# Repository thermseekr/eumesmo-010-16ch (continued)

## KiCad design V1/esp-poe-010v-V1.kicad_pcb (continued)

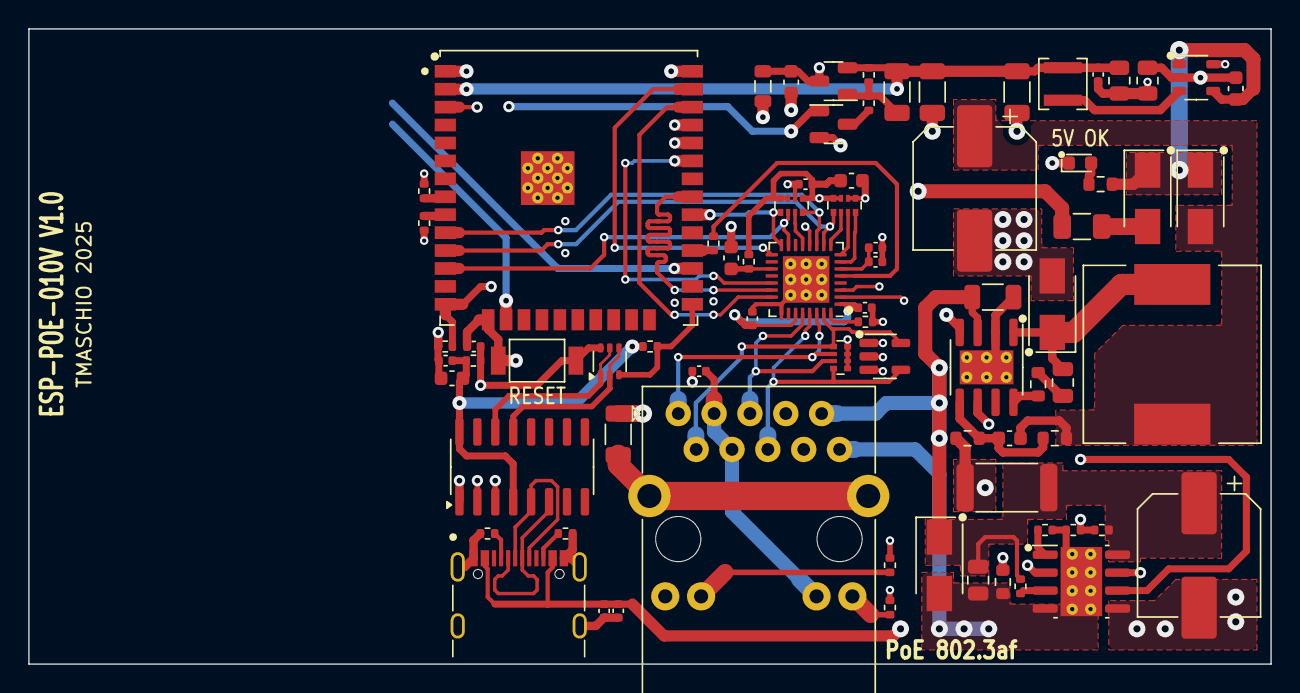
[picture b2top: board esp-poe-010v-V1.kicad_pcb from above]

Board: 4 copper layers, 88.0 x 45.0 mm, 77 parts (0 on the bottom side), 64 nets.

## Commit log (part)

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2025-12-13 Deleted unused files
2025-12-19 dev time
2026-06-18 Starting for an existing project.
2026-06-18 Development.
2026-06-18 Renamed all files to reflect the eumesmo branding.
2026-06-18 Restarting fresh
2026-06-19 Development
2026-06-24 V1.0.0
2026-06-24 Rename project from ESP-POE-010V to eumesmo-010-16ch
2026-06-27 Power and heartbeat leds repositioned.
